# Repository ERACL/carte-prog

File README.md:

Carte programmation
===================

Contient la CAO KiCAD de la carte programmation.
Cette carte sert à faire le lien entre les connecteurs de programmation présents sur les cartes électroniques et l'ICD.

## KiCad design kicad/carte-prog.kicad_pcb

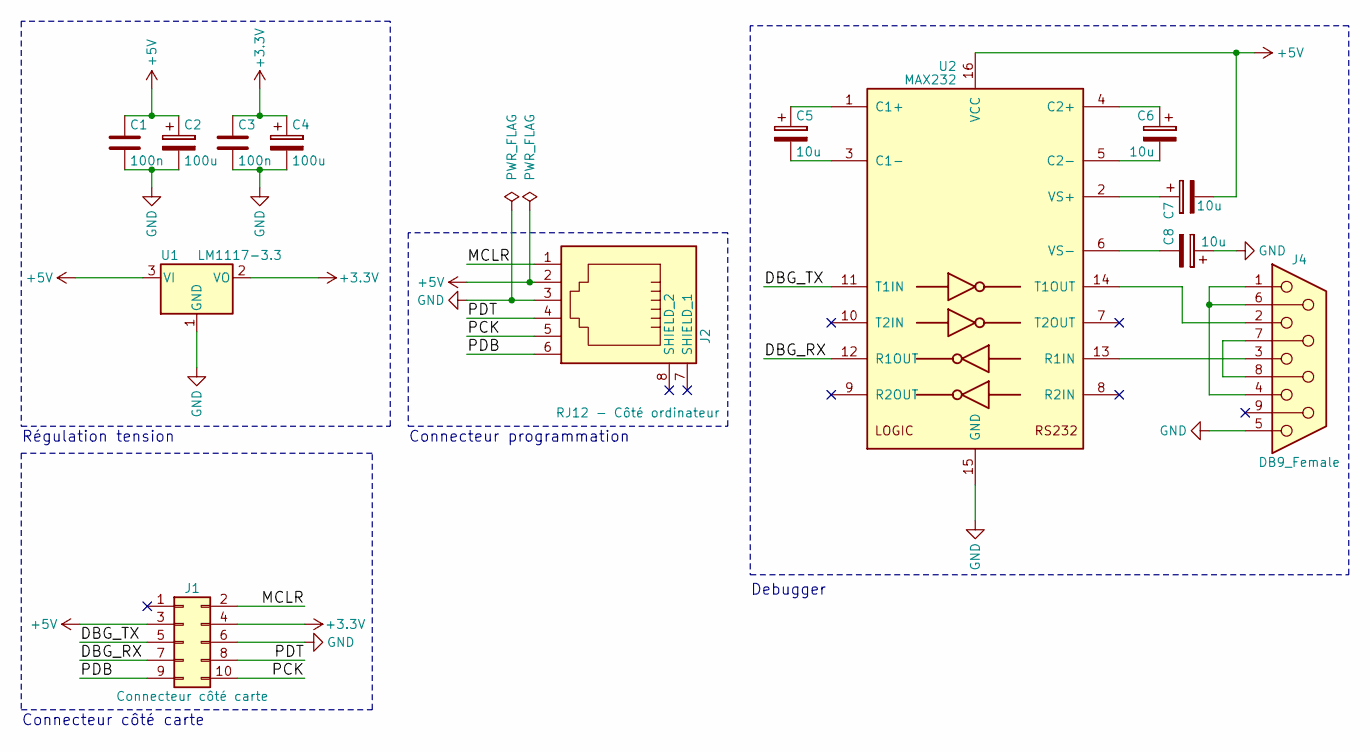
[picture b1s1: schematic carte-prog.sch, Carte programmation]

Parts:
C1, C3: 100n; C_Rect_L4.0mm_W2.5mm_P2.50mm
C2, C4: 100u; CP_Radial_D5.0mm_P2.50mm
C5, C6, C7, C8: 10u; CP_Radial_D5.0mm_P2.50mm
J1: Connecteur côté carte; Pin_Header_Straight_2x05_Pitch2.54mm
J2: RJ12 - Côté ordinateur; RJ12
J4: DB9_Female; DB9FC
U1: LM1117-3.3; TO-220_Horizontal
U2: MAX232; DIP-16_W7.62mm

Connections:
+3V3: C3.1, C4.1, J1.4, U1.2 (VO)
+5V: C1.1, C2.1, C7.2, J1.3, J2.2, U1.3 (VI), U2.16 (VCC)
/DBG_RX: J1.7, U2.12 (R1OUT)
/DBG_TX: J1.5, U2.11 (T1IN)
/MCLR: J1.2, J2.1
/PCK: J1.10, J2.5
/PDB: J1.9, J2.6
/PDT: J1.8, J2.4
GND: C1.2, C2.2, C3.2, C4.2, C8.1, J1.6, J2.3, J4.5, U1.1 (GND), U2.15 (GND)
unnamed: C5.1, U2.1 (C1+)
unnamed: C5.2, U2.3 (C1-)
unnamed: C6.1, U2.4 (C2+)
unnamed: C6.2, U2.5 (C2-)
unnamed: C7.1, U2.2 (VS+)
unnamed: C8.2, U2.6 (VS-)
unnamed: J4.1, J4.4, J4.6
unnamed: J4.2, U2.14 (T1OUT)
unnamed: J4.3, U2.13 (R1IN)
unnamed: J4.7, J4.8

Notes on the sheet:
Régulation tension
Connecteur programmation
Connecteur côté carte
Debugger

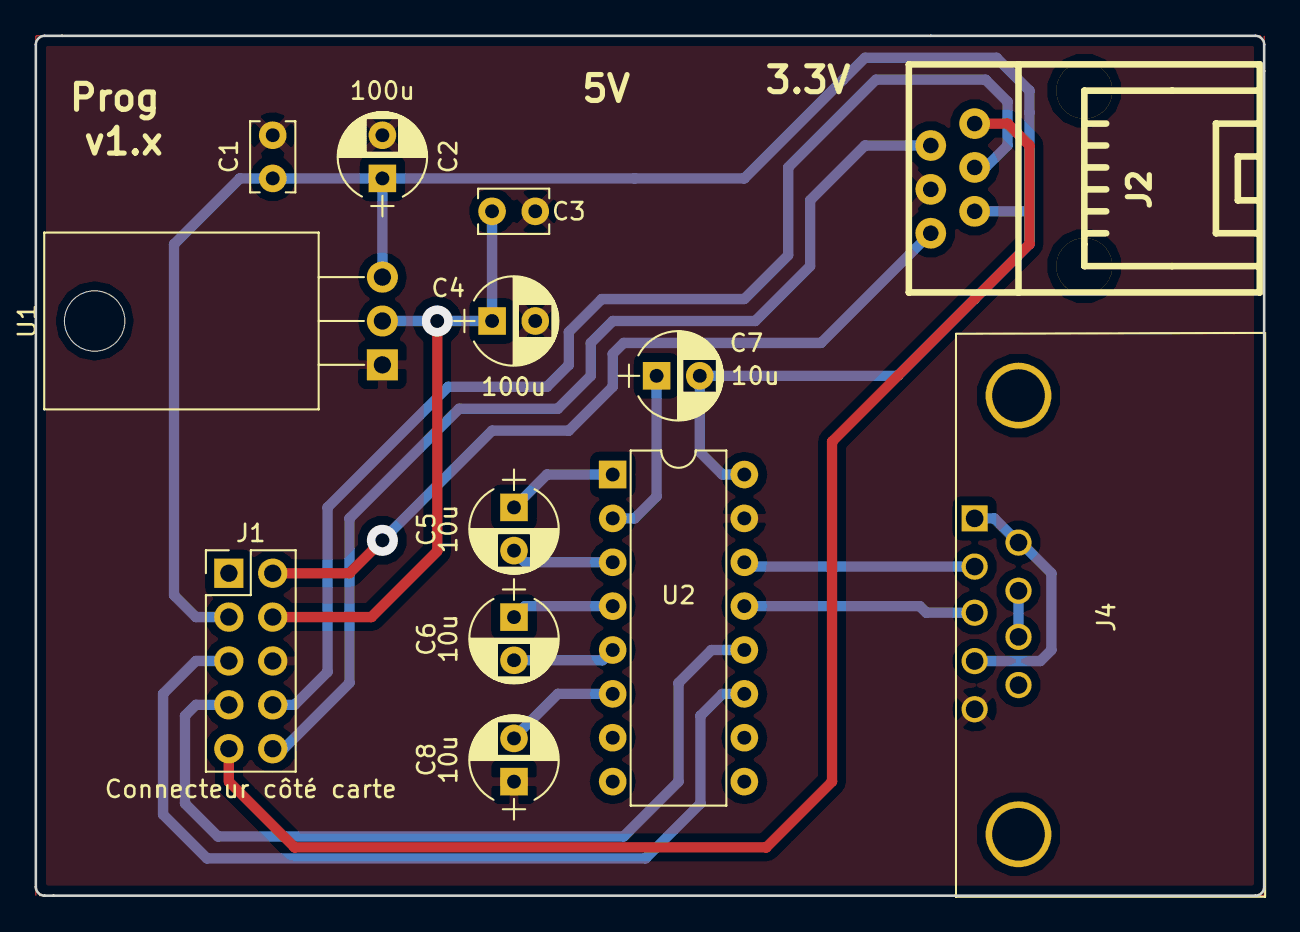
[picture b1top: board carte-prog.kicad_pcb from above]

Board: 2 copper layers, 71.1 x 49.8 mm, 13 parts (0 on the bottom side), 19 nets.

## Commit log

2018-03-24 Mise en forme du fichier README.md
2018-03-24 Création du projet KiCAD
2018-04-10 Premier jet
2018-04-20 Ajout d'un max232
2018-04-22 Modification pour ignorer les fichiers d'export Gerber
2018-04-22 Modification des caches
2018-04-22 Modification des cartouches en vue de la release
2018-04-23 Correction sens condensateur V-
2018-04-23 Préparation des fichiers à la release
2018-04-23 Enlèvement connecteur choix alim
